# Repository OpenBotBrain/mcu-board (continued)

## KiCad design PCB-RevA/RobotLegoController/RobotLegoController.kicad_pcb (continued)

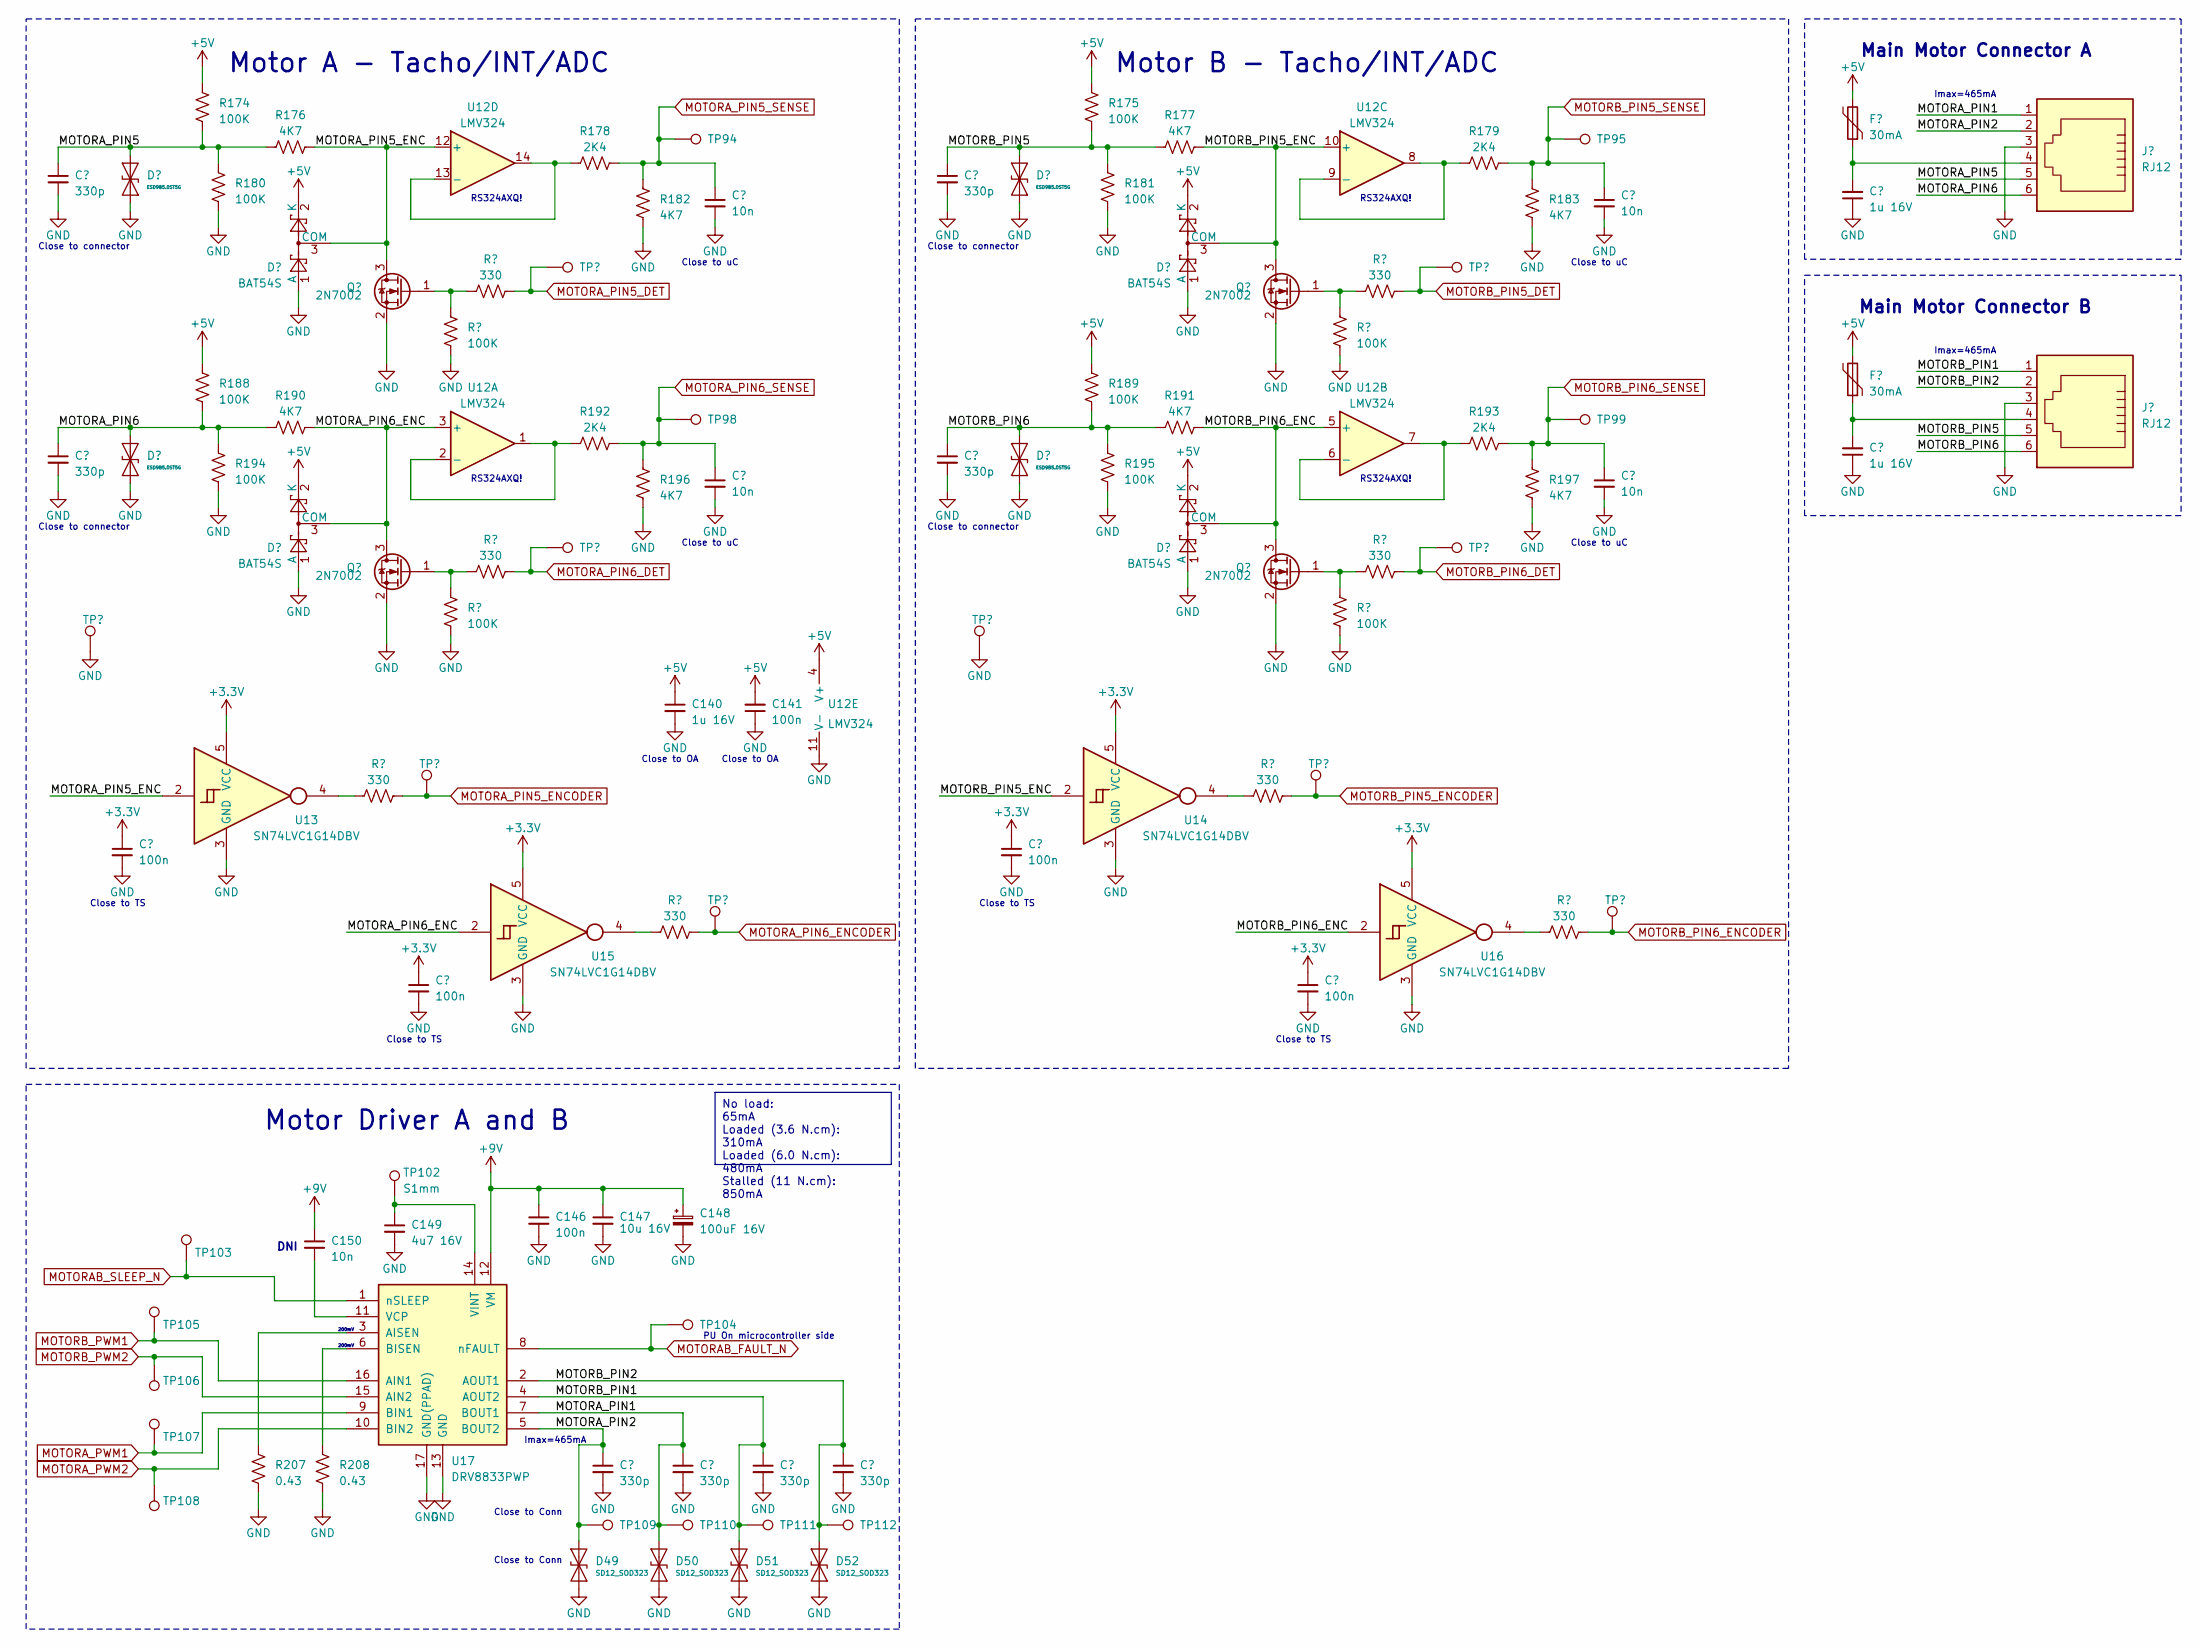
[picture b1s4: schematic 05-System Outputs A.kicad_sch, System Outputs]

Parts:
C118, C150: 10n; C_0402_1005Metric
C130, C131, C136, C137, C151, C152, C153, C154: 330p; C_0402_1005Metric
C132, C135, C140: 1u 16V; C_0603_1608Metric
C141, C142, C143, C144, C145, C146: 100n; C_0402_1005Metric
C147: 10u 16V; C_0805_2012Metric
C148: 100uF 16V; CP_Elec_6.3x5.2
C149: 4u7 16V; C_0603_1608Metric
D41, D42, D45, D46: ESD9B5.0ST5G; D_SOD-923
D43, D44, D47, D48: BAT54S; SOT-23
D49, D50, D51, D52: SD12_SOD323; D_SOD-323
F7, F8: 30mA; R_0603_1608Metric
J11, J12: RJ12; RJ12_Amphenol_54601
Q29, Q30, Q31, Q32: 2N7002; SOT-23
R174, R175, R180, R181, R186, R187, R188, R189, R194, R195, R200, R201: 100K; R_0402_1005Metric
R176, R177, R182, R183, R190, R191, R196, R197: 4K7; R_0402_1005Metric
R178, R179, R192, R193: 2K4; R_0402_1005Metric
R184, R185, R198, R199, R202, R203, R204, R205: 330; R_0402_1005Metric
R207, R208: 0.43; R_0805_2012Metric
TP16, TP20, TP94, TP95, TP96, TP97, TP98, TP99, TP100, TP101, TP102, TP103, TP104, TP105, TP106, TP107, TP108, TP109, TP110, TP111, TP112, TP134, TP135, TP142, TP143: S1mm; TestPoint_Pad_1.0x1.0mm
U12: LMV324; SOIC-14_3.9x8.7mm_P1.27mm
U13, U14, U15, U16: SN74LVC1G14DBV; SOT-23-5
U17: DRV8833PWP; HTSSOP-16-1EP_4.4x5mm_P0.65mm_EP3.4x5mm_Mask2.46x2.31mm_The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

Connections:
+3.3V: C142.1, C143.1, C144.1, C145.1, U13.5 (VCC), U14.5 (VCC), U15.5 (VCC), U16.5 (VCC); also elsewhere on the board
+9V: C146.1, C147.1, C148.1, C150.1, U17.12 (VM); also elsewhere on the board
/05-System Outputs A/MOTORA_PIN1: C152.1, D50.2 (A2), J11.1, TP110.1, U17.7 (BOUT1)
/05-System Outputs A/MOTORA_PIN2: C151.1, D49.2 (A2), J11.2, TP109.1, U17.5 (BOUT2)
/05-System Outputs A/MOTORA_PIN5: C130.1, D41.2 (A2), J11.5, R174.1, R176.2, R180.2
/05-System Outputs A/MOTORA_PIN5_ENC: D43.3 (COM), Q29.3 (D), R176.1, U12.12 (+), U13.2
/05-System Outputs A/MOTORA_PIN6: C136.1, D45.2 (A2), J11.6, R188.1, R190.2, R194.2
/05-System Outputs A/MOTORA_PIN6_ENC: D47.3 (COM), Q31.3 (D), R190.1, U12.3 (+), U15.2
/05-System Outputs A/MOTORB_PIN1: C153.1, D51.2 (A2), J12.1, TP111.1, U17.4 (AOUT2)
/05-System Outputs A/MOTORB_PIN2: C154.1, D52.2 (A2), J12.2, TP112.1, U17.2 (AOUT1)
/05-System Outputs A/MOTORB_PIN5: C131.1, D42.2 (A2), J12.5, R175.1, R177.2, R181.2
/05-System Outputs A/MOTORB_PIN5_ENC: D44.3 (COM), Q30.3 (D), R177.1, U12.10 (+), U14.2
/05-System Outputs A/MOTORB_PIN6: C137.1, D46.2 (A2), J12.6, R189.1, R191.2, R195.2
/05-System Outputs A/MOTORB_PIN6_ENC: D48.3 (COM), Q32.3 (D), R191.1, U12.5 (+), U16.2
MOTORAB_FAULT_N: TP104.1, U17.8 (nFAULT); also elsewhere on the board
MOTORAB_SLEEP_N: TP103.1, U17.1 (nSLEEP); also elsewhere on the board
MOTORA_PIN5_DET: R184.1, TP96.1
MOTORA_PIN5_ENCODER: R202.1, TP134.1; also elsewhere on the board
MOTORA_PIN6_DET: R198.1, TP100.1; also elsewhere on the board
MOTORA_PIN6_ENCODER: R204.1, TP135.1; also elsewhere on the board
MOTORA_PWM1: TP107.1, U17.9 (BIN1); also elsewhere on the board
MOTORA_PWM2: TP108.1, U17.10 (BIN2); also elsewhere on the board
MOTORB_PIN5_DET: R185.1, TP97.1
MOTORB_PIN6_DET: R199.1, TP101.1
MOTORB_PIN6_ENCODER: R205.1, TP20.1; also elsewhere on the board
MOTORB_PWM1: TP105.1, U17.16 (AIN1); also elsewhere on the board
MOTORB_PWM2: TP106.1, U17.15 (AIN2); also elsewhere on the board
unnamed: C132.2, F7.1, J11.4
unnamed: C135.2, F8.1, J12.4
unnamed: Q29.1 (G), R184.2, R186.2
unnamed: Q30.1 (G), R185.2, R187.2
unnamed: Q31.1 (G), R198.2, R200.2
unnamed: Q32.1 (G), R199.2, R201.2
unnamed: R202.2, U13.4
unnamed: R203.2, U14.4
unnamed: R204.2, U15.4
unnamed: R205.2, U16.4
unnamed: R192.1, U12.1, U12.2 (-)
unnamed: R193.1, U12.6 (-), U12.7
unnamed: R179.1, U12.8, U12.9 (-)
unnamed: R178.1, U12.13 (-), U12.14
unnamed: R207.2, U17.3 (AISEN)
unnamed: R208.2, U17.6 (BISEN)
unnamed: C150.2, U17.11 (VCP)
unnamed: C149.1, TP102.1, U17.14 (VINT)

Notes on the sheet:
No load: 65mA Loaded (3.6 N.cm): 310mA Loaded (6.0 N.cm): 480mA Stalled (11 N.cm): 850mA
RS324AXQ!
Motor A - Tacho/INT/ADC
Close to connector
Close to Conn
Close to uC
200mV
Close to TS
Main Motor Connector B
Motor Driver A and B
Imax=465mA
DNI
Main Motor Connector A
PU On microcontroller side
Close to OA
Motor B - Tacho/INT/ADC

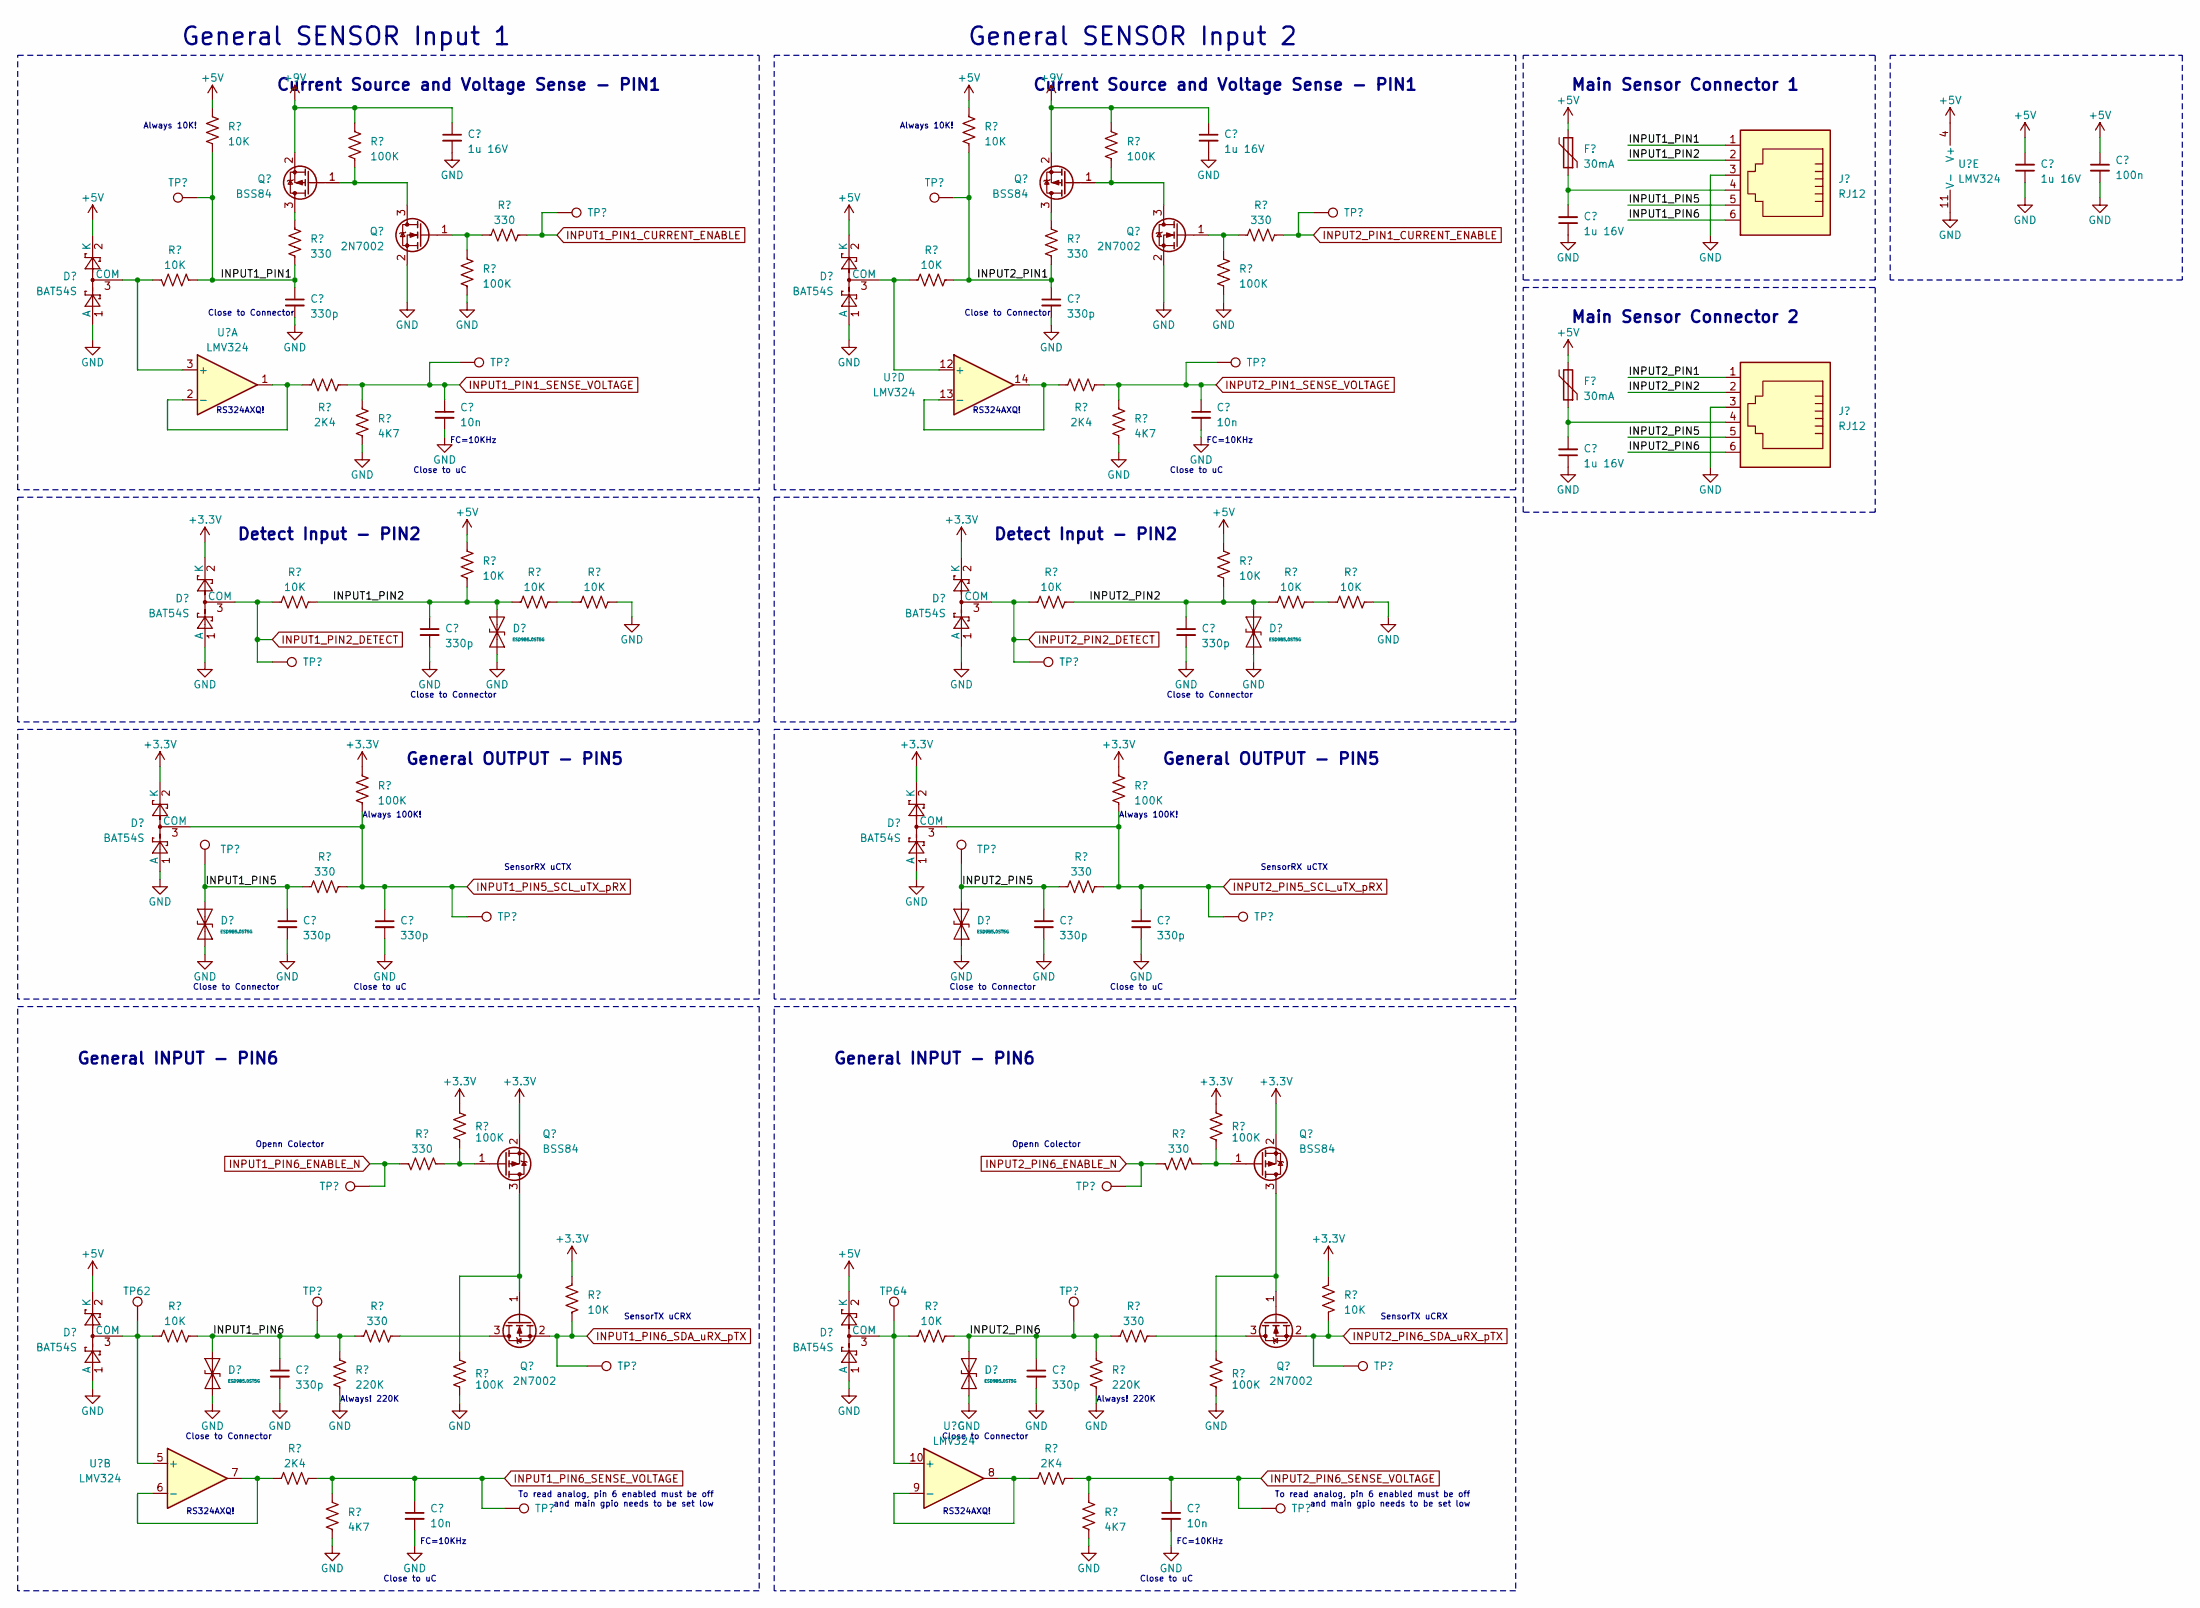
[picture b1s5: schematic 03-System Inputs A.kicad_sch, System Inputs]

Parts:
C90, C91, C92, C94, C99: 1u 16V; C_0603_1608Metric
C93: 100n; C_0402_1005Metric
C95, C96, C100, C101, C102, C103, C104, C105, C106, C107: 330p; C_0402_1005Metric
C97, C98, C108, C109: 10n; C_0402_1005Metric
D13, D14, D15, D16, D19, D20, D23, D24: BAT54S; SOT-23
D17, D18, D21, D22, D25, D26: ESD9B5.0ST5G; D_SOD-923
F3, F4: 30mA; R_0603_1608Metric
J7, J8: RJ12; RJ12_Amphenol_54601
Q5, Q6, Q9, Q10: BSS84; SOT-23
Q7, Q8, Q15, Q16: 2N7002; SOT-23
R74, R75, R84, R85, R90, R91, R92, R93, R94, R95, R96, R97, R110, R111, R112, R114: 10K; R_0402_1005Metric
R76, R77, R82, R83, R98, R99, R102, R103, R117, R119: 100K; R_0402_1005Metric
R78, R79, R80, R81, R100, R101, R104, R105, R113, R115: 330; R_0402_1005Metric
R86, R87, R120, R121: 2K4; R_0402_1005Metric
R88, R89, R122, R123: 4K7; R_0402_1005Metric
R116, R118: 220K; R_0402_1005Metric
TP46, TP47, TP48, TP49, TP50, TP51, TP52, TP53, TP54, TP55, TP56, TP57, TP59, TP60, TP62, TP63, TP64, TP65, TP66, TP67, TP68, TP69: S1mm; TestPoint_Pad_1.0x1.0mm
U10: LMV324; SOIC-14_3.9x8.7mm_P1.27mm

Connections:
+3.3V: D15.2 (K), D16.2 (K), D19.2 (K), D20.2 (K), Q9.2 (S), Q10.2 (S), R98.2, R99.2, R102.2, R103.2, R110.1, R111.1; also elsewhere on the board
+9V: C90.1, C91.1, Q5.2 (S), Q6.2 (S), R76.2, R77.2; also elsewhere on the board
/03-System Inputs A/INPUT1_PIN1: C95.1, J7.1, R74.1, R80.1, R84.2, TP46.1
/03-System Inputs A/INPUT1_PIN2: C100.1, D17.2 (A2), J7.2, R90.1, R92.2, R93.2
/03-System Inputs A/INPUT1_PIN5: C102.1, D21.2 (A2), J7.5, R100.2, TP54.1
/03-System Inputs A/INPUT1_PIN6: C106.1, D25.2 (A2), J7.6, R112.2, R113.2, R116.1, TP63.1
/03-System Inputs A/INPUT2_PIN1: C96.1, J8.1, R75.1, R81.1, R85.1, TP47.1
/03-System Inputs A/INPUT2_PIN2: C101.1, D18.2 (A2), J8.2, R91.1, R95.2, R96.2
/03-System Inputs A/INPUT2_PIN5: C104.1, D22.2 (A2), J8.5, R101.2, TP55.1
/03-System Inputs A/INPUT2_PIN6: C107.1, D26.2 (A2), J8.6, R114.2, R115.2, R118.1, TP65.1
INPUT1_PIN1_CURRENT_ENABLE: R78.1, TP48.1; also elsewhere on the board
INPUT1_PIN1_SENSE_VOLTAGE: C97.1, R86.2, R88.1, TP50.1; also elsewhere on the board
INPUT1_PIN2_DETECT: D15.3 (COM), R92.1, TP52.1; also elsewhere on the board
INPUT1_PIN5_SCL_uTX_pRX: C103.1, D19.3 (COM), R98.1, R100.1, TP56.1; also elsewhere on the board
INPUT1_PIN6_ENABLE_N: R104.1, TP60.1; also elsewhere on the board
INPUT1_PIN6_SDA_uRX_pTX: Q15.2 (S), R110.2, TP66.1; also elsewhere on the board
INPUT1_PIN6_SENSE_VOLTAGE: C108.1, R120.2, R122.1, TP68.1; also elsewhere on the board
INPUT2_PIN1_CURRENT_ENABLE: R79.1, TP49.1; also elsewhere on the board
INPUT2_PIN1_SENSE_VOLTAGE: C98.1, R87.2, R89.1, TP51.1; also elsewhere on the board
INPUT2_PIN2_DETECT: D16.3 (COM), R95.1, TP53.1; also elsewhere on the board
INPUT2_PIN5_SCL_uTX_pRX: C105.1, D20.3 (COM), R99.1, R101.1, TP57.1; also elsewhere on the board
INPUT2_PIN6_ENABLE_N: R105.1, TP59.1; also elsewhere on the board
INPUT2_PIN6_SDA_uRX_pTX: Q16.2 (S), R111.2, TP67.1; also elsewhere on the board
INPUT2_PIN6_SENSE_VOLTAGE: C109.1, R121.2, R123.1, TP69.1; also elsewhere on the board
unnamed: C94.2, F3.1, J7.4
unnamed: C99.2, F4.1, J8.4
unnamed: D13.3 (COM), R84.1, U10.3 (+)
unnamed: D14.3 (COM), R85.2, U10.12 (+)
unnamed: D23.3 (COM), R112.1, TP62.1, U10.5 (+)
unnamed: D24.3 (COM), R114.1, TP64.1, U10.10 (+)
unnamed: Q5.3 (D), R80.2
unnamed: Q5.1 (G), Q7.3 (D), R76.1
unnamed: Q6.3 (D), R81.2
unnamed: Q6.1 (G), Q8.3 (D), R77.1
unnamed: Q7.1 (G), R78.2, R82.2
unnamed: Q8.1 (G), R79.2, R83.2
unnamed: Q9.1 (G), R103.1, R105.2
unnamed: Q10.3 (D), Q15.1 (G), R117.2
unnamed: Q10.1 (G), R102.1, R104.2
unnamed: Q15.3 (D), R113.1
unnamed: Q16.3 (D), R115.1
unnamed: Q9.3 (D), Q16.1 (G), R119.2
unnamed: R93.1, R94.2
unnamed: R96.1, R97.2
unnamed: R86.1, U10.1, U10.2 (-)
unnamed: R120.1, U10.6 (-), U10.7
unnamed: R121.1, U10.8, U10.9 (-)
unnamed: R87.1, U10.13 (-), U10.14

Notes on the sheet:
RS324AXQ!
General OUTPUT - PIN5
Close to Connector
Main Sensor Connector 2
Close to uC
FC=10KHz
General SENSOR Input 2
Detect Input - PIN2
Main Sensor Connector 1
To read analog, pin 6 enabled must be off and main gpio needs to be set low
Openn Colector
Current Source and Voltage Sense - PIN1
Always 100K!
General SENSOR Input 1
General INPUT - PIN6
Always 10K!
SensorRX uCTX
Always! 220K
SensorTX uCRX

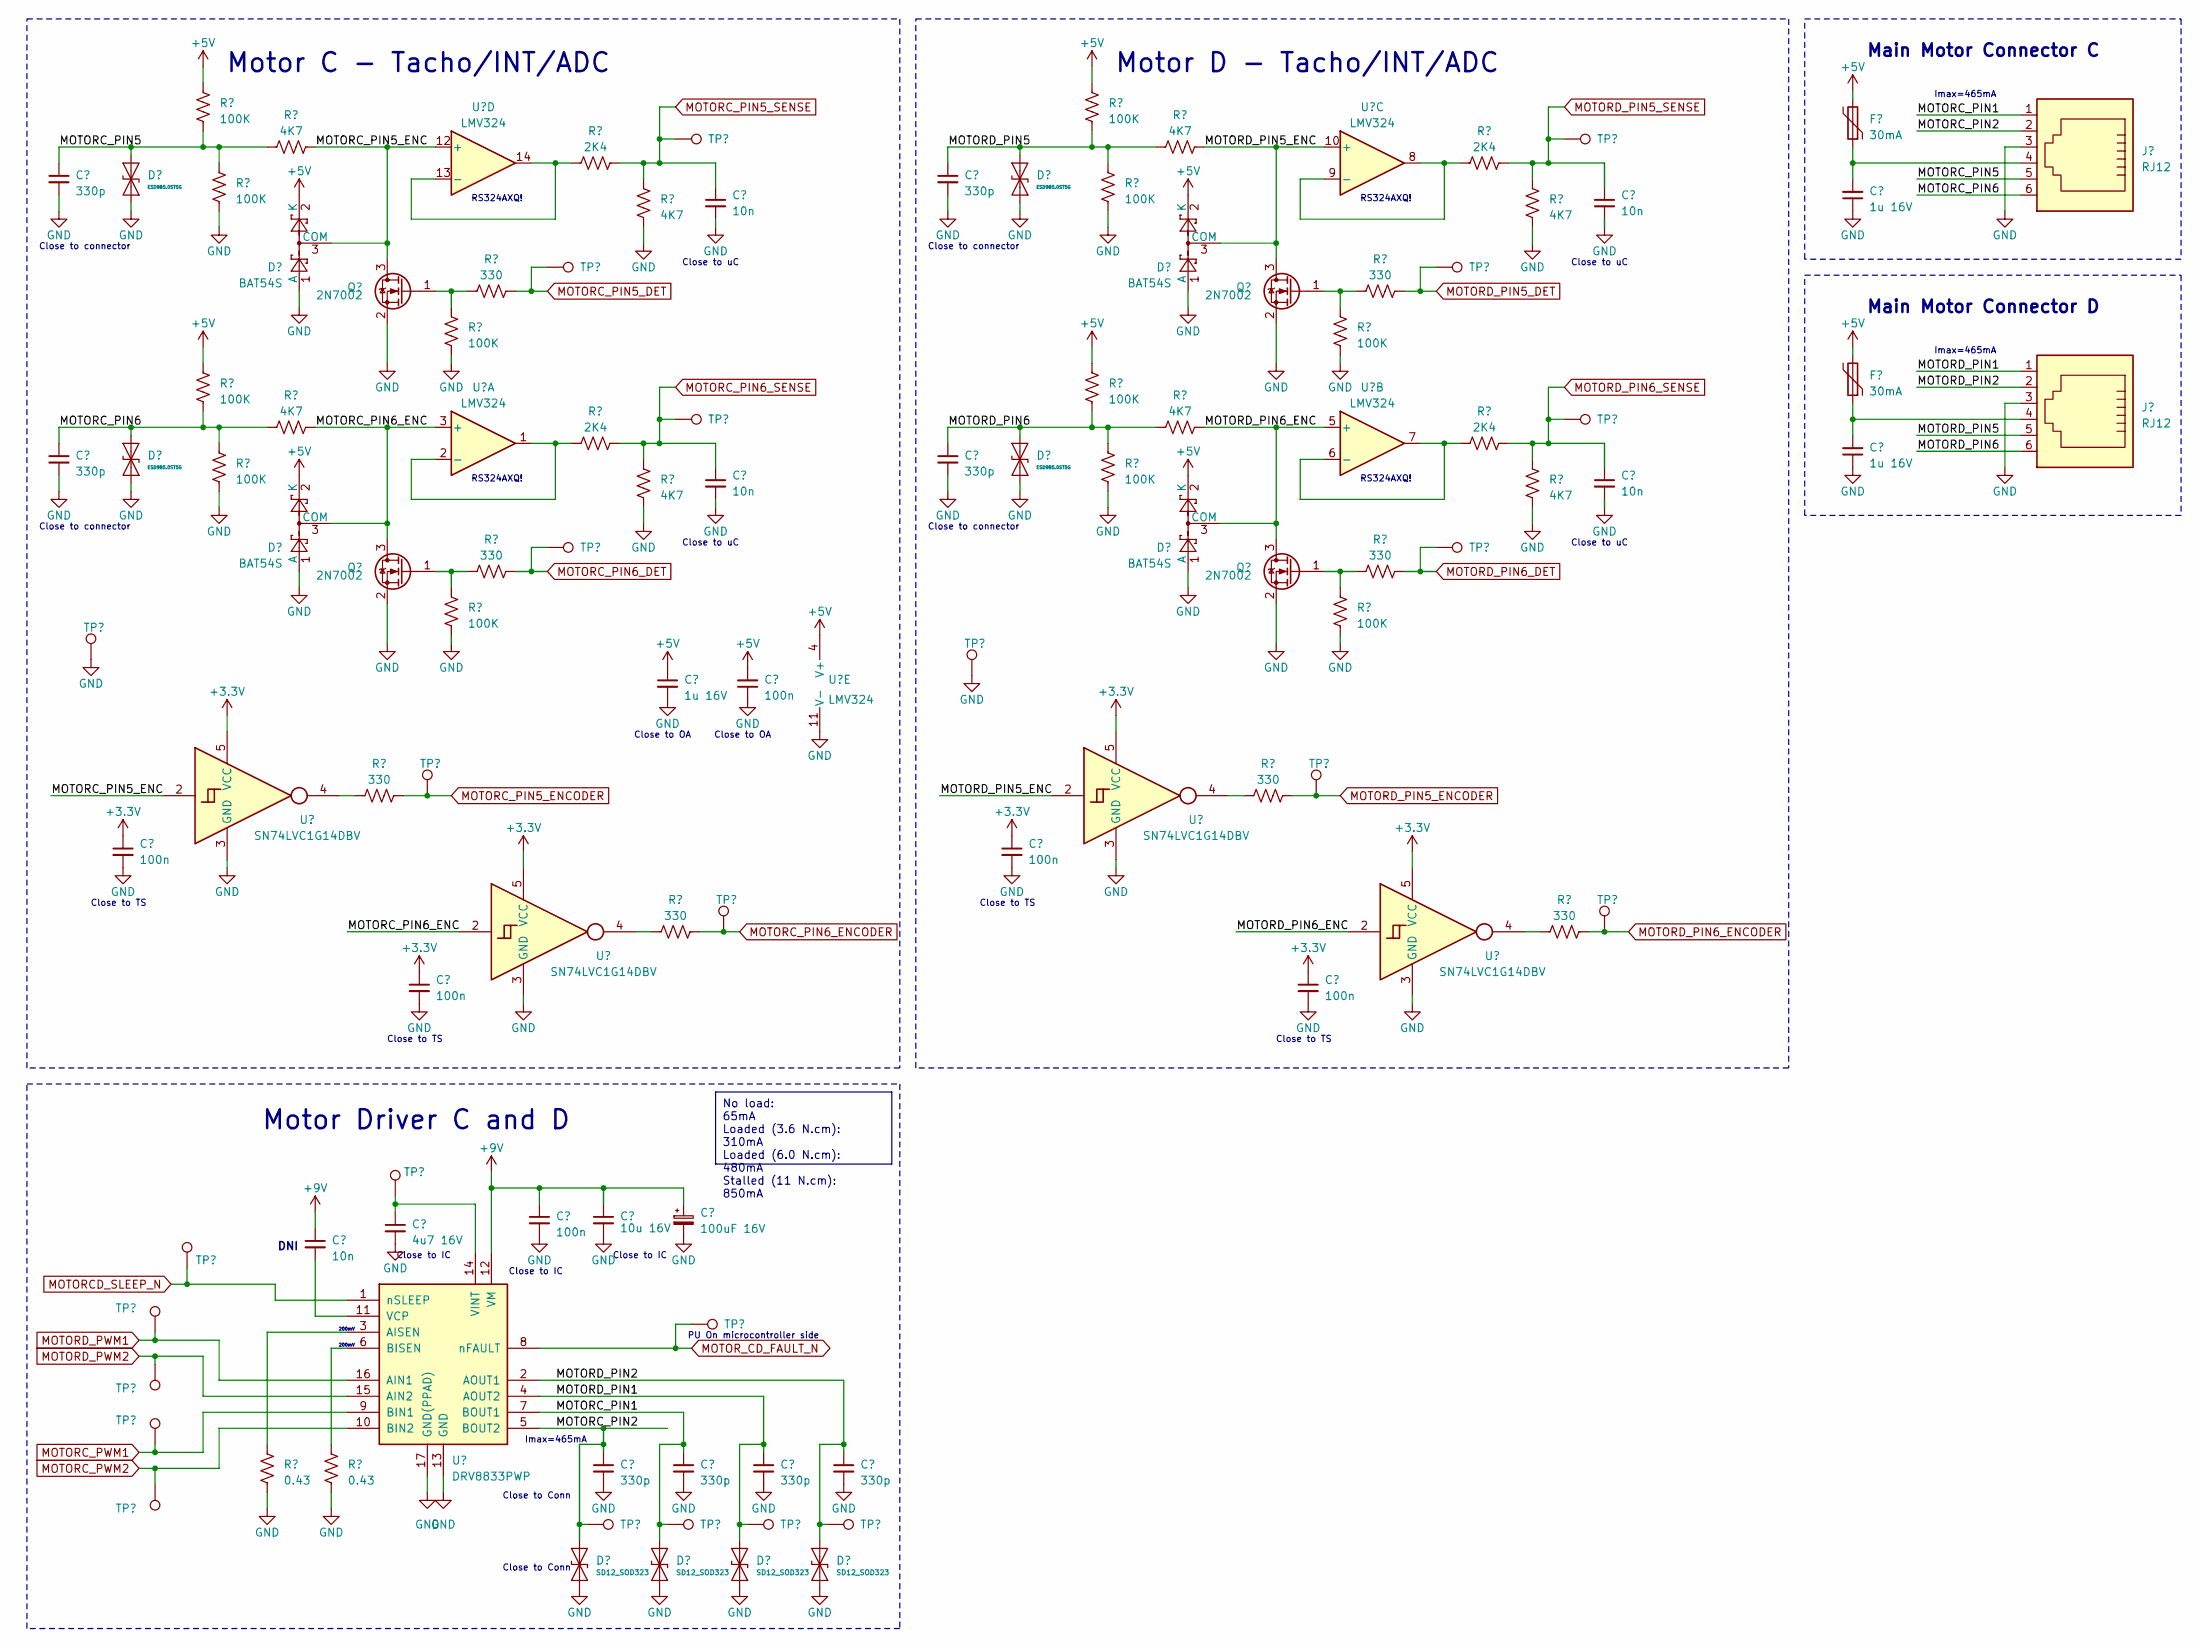
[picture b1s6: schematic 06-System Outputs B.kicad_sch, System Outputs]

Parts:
C118, C175: 10n; C_0402_1005Metric
C155, C156, C161, C162, C176, C177, C178, C179: 330p; C_0402_1005Metric
C157, C160, C165: 1u 16V; C_0603_1608Metric
C166, C167, C168, C169, C170, C171: 100n; C_0402_1005Metric
C172: 10u 16V; C_0805_2012Metric
C173: 100uF 16V; CP_Elec_6.3x5.2
C174: 4u7 16V; C_0603_1608Metric
D53, D54, D57, D58: ESD9B5.0ST5G; D_SOD-923
D55, D56, D59, D60: BAT54S; SOT-23
D61, D62, D63, D64: SD12_SOD323; D_SOD-323
F9, F10: 30mA; R_0603_1608Metric
J13, J14: RJ12; RJ12_Amphenol_54601
Q33, Q34, Q35, Q36: 2N7002; SOT-23
R209, R210, R215, R216, R221, R222, R223, R224, R229, R230, R235, R236: 100K; R_0402_1005Metric
R211, R212, R217, R218, R225, R226, R231, R232: 4K7; R_0402_1005Metric
R213, R214, R227, R228: 2K4; R_0402_1005Metric
R219, R220, R233, R234, R237, R238, R239, R240: 330; R_0402_1005Metric
R242, R243: 0.43; R_0805_2012Metric
TP16, TP113, TP114, TP115, TP116, TP117, TP118, TP119, TP120, TP121, TP122, TP123, TP124, TP125, TP126, TP127, TP128, TP129, TP130, TP131: S1mm; TestPoint_Pad_1.0x1.0mm
U18: LMV324; SOIC-14_3.9x8.7mm_P1.27mm
U19, U20, U21, U22: SN74LVC1G14DBV; SOT-23-5
U23: DRV8833PWP; HTSSOP-16-1EP_4.4x5mm_P0.65mm_EP3.4x5mm_Mask2.46x2.31mm_The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

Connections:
+3.3V: C167.1, C168.1, C169.1, C170.1, U19.5 (VCC), U20.5 (VCC), U21.5 (VCC), U22.5 (VCC); also elsewhere on the board
+9V: C171.1, C172.1, C173.1, C175.1, U23.12 (VM); also elsewhere on the board
/06-System Outputs B/MOTORC_PIN1: C177.1, D62.2 (A2), J13.1, TP129.1, U23.7 (BOUT1)
/06-System Outputs B/MOTORC_PIN2: C176.1, D61.2 (A2), J13.2, TP128.1, U23.5 (BOUT2)
/06-System Outputs B/MOTORC_PIN5: C155.1, D53.2 (A2), J13.5, R209.1, R211.2, R215.2
/06-System Outputs B/MOTORC_PIN5_ENC: D55.3 (COM), Q33.3 (D), R211.1, U18.12 (+), U19.2
/06-System Outputs B/MOTORC_PIN6: C161.1, D57.2 (A2), J13.6, R223.1, R225.2, R229.2
/06-System Outputs B/MOTORC_PIN6_ENC: D59.3 (COM), Q35.3 (D), R225.1, U18.3 (+), U21.2
/06-System Outputs B/MOTORD_PIN1: C178.1, D63.2 (A2), J14.1, TP130.1, U23.4 (AOUT2)
/06-System Outputs B/MOTORD_PIN2: C179.1, D64.2 (A2), J14.2, TP131.1, U23.2 (AOUT1)
/06-System Outputs B/MOTORD_PIN5: C156.1, D54.2 (A2), J14.5, R210.1, R212.2, R216.2
/06-System Outputs B/MOTORD_PIN5_ENC: D56.3 (COM), Q34.3 (D), R212.1, U18.10 (+), U20.2
/06-System Outputs B/MOTORD_PIN6: C162.1, D58.2 (A2), J14.6, R224.1, R226.2, R230.2
/06-System Outputs B/MOTORD_PIN6_ENC: D60.3 (COM), Q36.3 (D), R226.1, U18.5 (+), U22.2
MOTORCD_SLEEP_N: TP122.1, U23.1 (nSLEEP); also elsewhere on the board
MOTORC_PIN5_DET: R219.1, TP115.1; also elsewhere on the board
MOTORC_PIN6_DET: R233.1, TP119.1; also elsewhere on the board
MOTORC_PWM1: TP126.1, U23.9 (BIN1); also elsewhere on the board
MOTORC_PWM2: TP127.1, U23.10 (BIN2); also elsewhere on the board
MOTORD_PIN5_DET: R220.1, TP116.1; also elsewhere on the board
MOTORD_PIN6_DET: R234.1, TP120.1; also elsewhere on the board
MOTORD_PWM1: TP124.1, U23.16 (AIN1); also elsewhere on the board
MOTORD_PWM2: TP125.1, U23.15 (AIN2); also elsewhere on the board
MOTOR_CD_FAULT_N: TP123.1, U23.8 (nFAULT)
unnamed: C157.2, F9.1, J13.4
unnamed: C160.2, F10.1, J14.4
unnamed: Q33.1 (G), R219.2, R221.2
unnamed: Q34.1 (G), R220.2, R222.2
unnamed: Q35.1 (G), R233.2, R235.2
unnamed: Q36.1 (G), R234.2, R236.2
unnamed: R237.2, U19.4
unnamed: R238.2, U20.4
unnamed: R239.2, U21.4
unnamed: R240.2, U22.4
unnamed: R227.1, U18.1, U18.2 (-)
unnamed: R228.1, U18.6 (-), U18.7
unnamed: R214.1, U18.8, U18.9 (-)
unnamed: R213.1, U18.13 (-), U18.14
unnamed: R242.2, U23.3 (AISEN)
unnamed: R243.2, U23.6 (BISEN)
unnamed: C175.2, U23.11 (VCP)
unnamed: C174.1, TP121.1, U23.14 (VINT)

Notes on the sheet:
No load: 65mA Loaded (3.6 N.cm): 310mA Loaded (6.0 N.cm): 480mA Stalled (11 N.cm): 850mA
Close to IC
Close to TS
200mV
RS324AXQ!
Close to connector
Main Motor Connector D
Close to uC
Close to OA
Close to Conn
DNI
Motor C - Tacho/INT/ADC
Imax=465mA
Motor Driver C and D
PU On microcontroller side
Main Motor Connector C
Motor D - Tacho/INT/ADC
